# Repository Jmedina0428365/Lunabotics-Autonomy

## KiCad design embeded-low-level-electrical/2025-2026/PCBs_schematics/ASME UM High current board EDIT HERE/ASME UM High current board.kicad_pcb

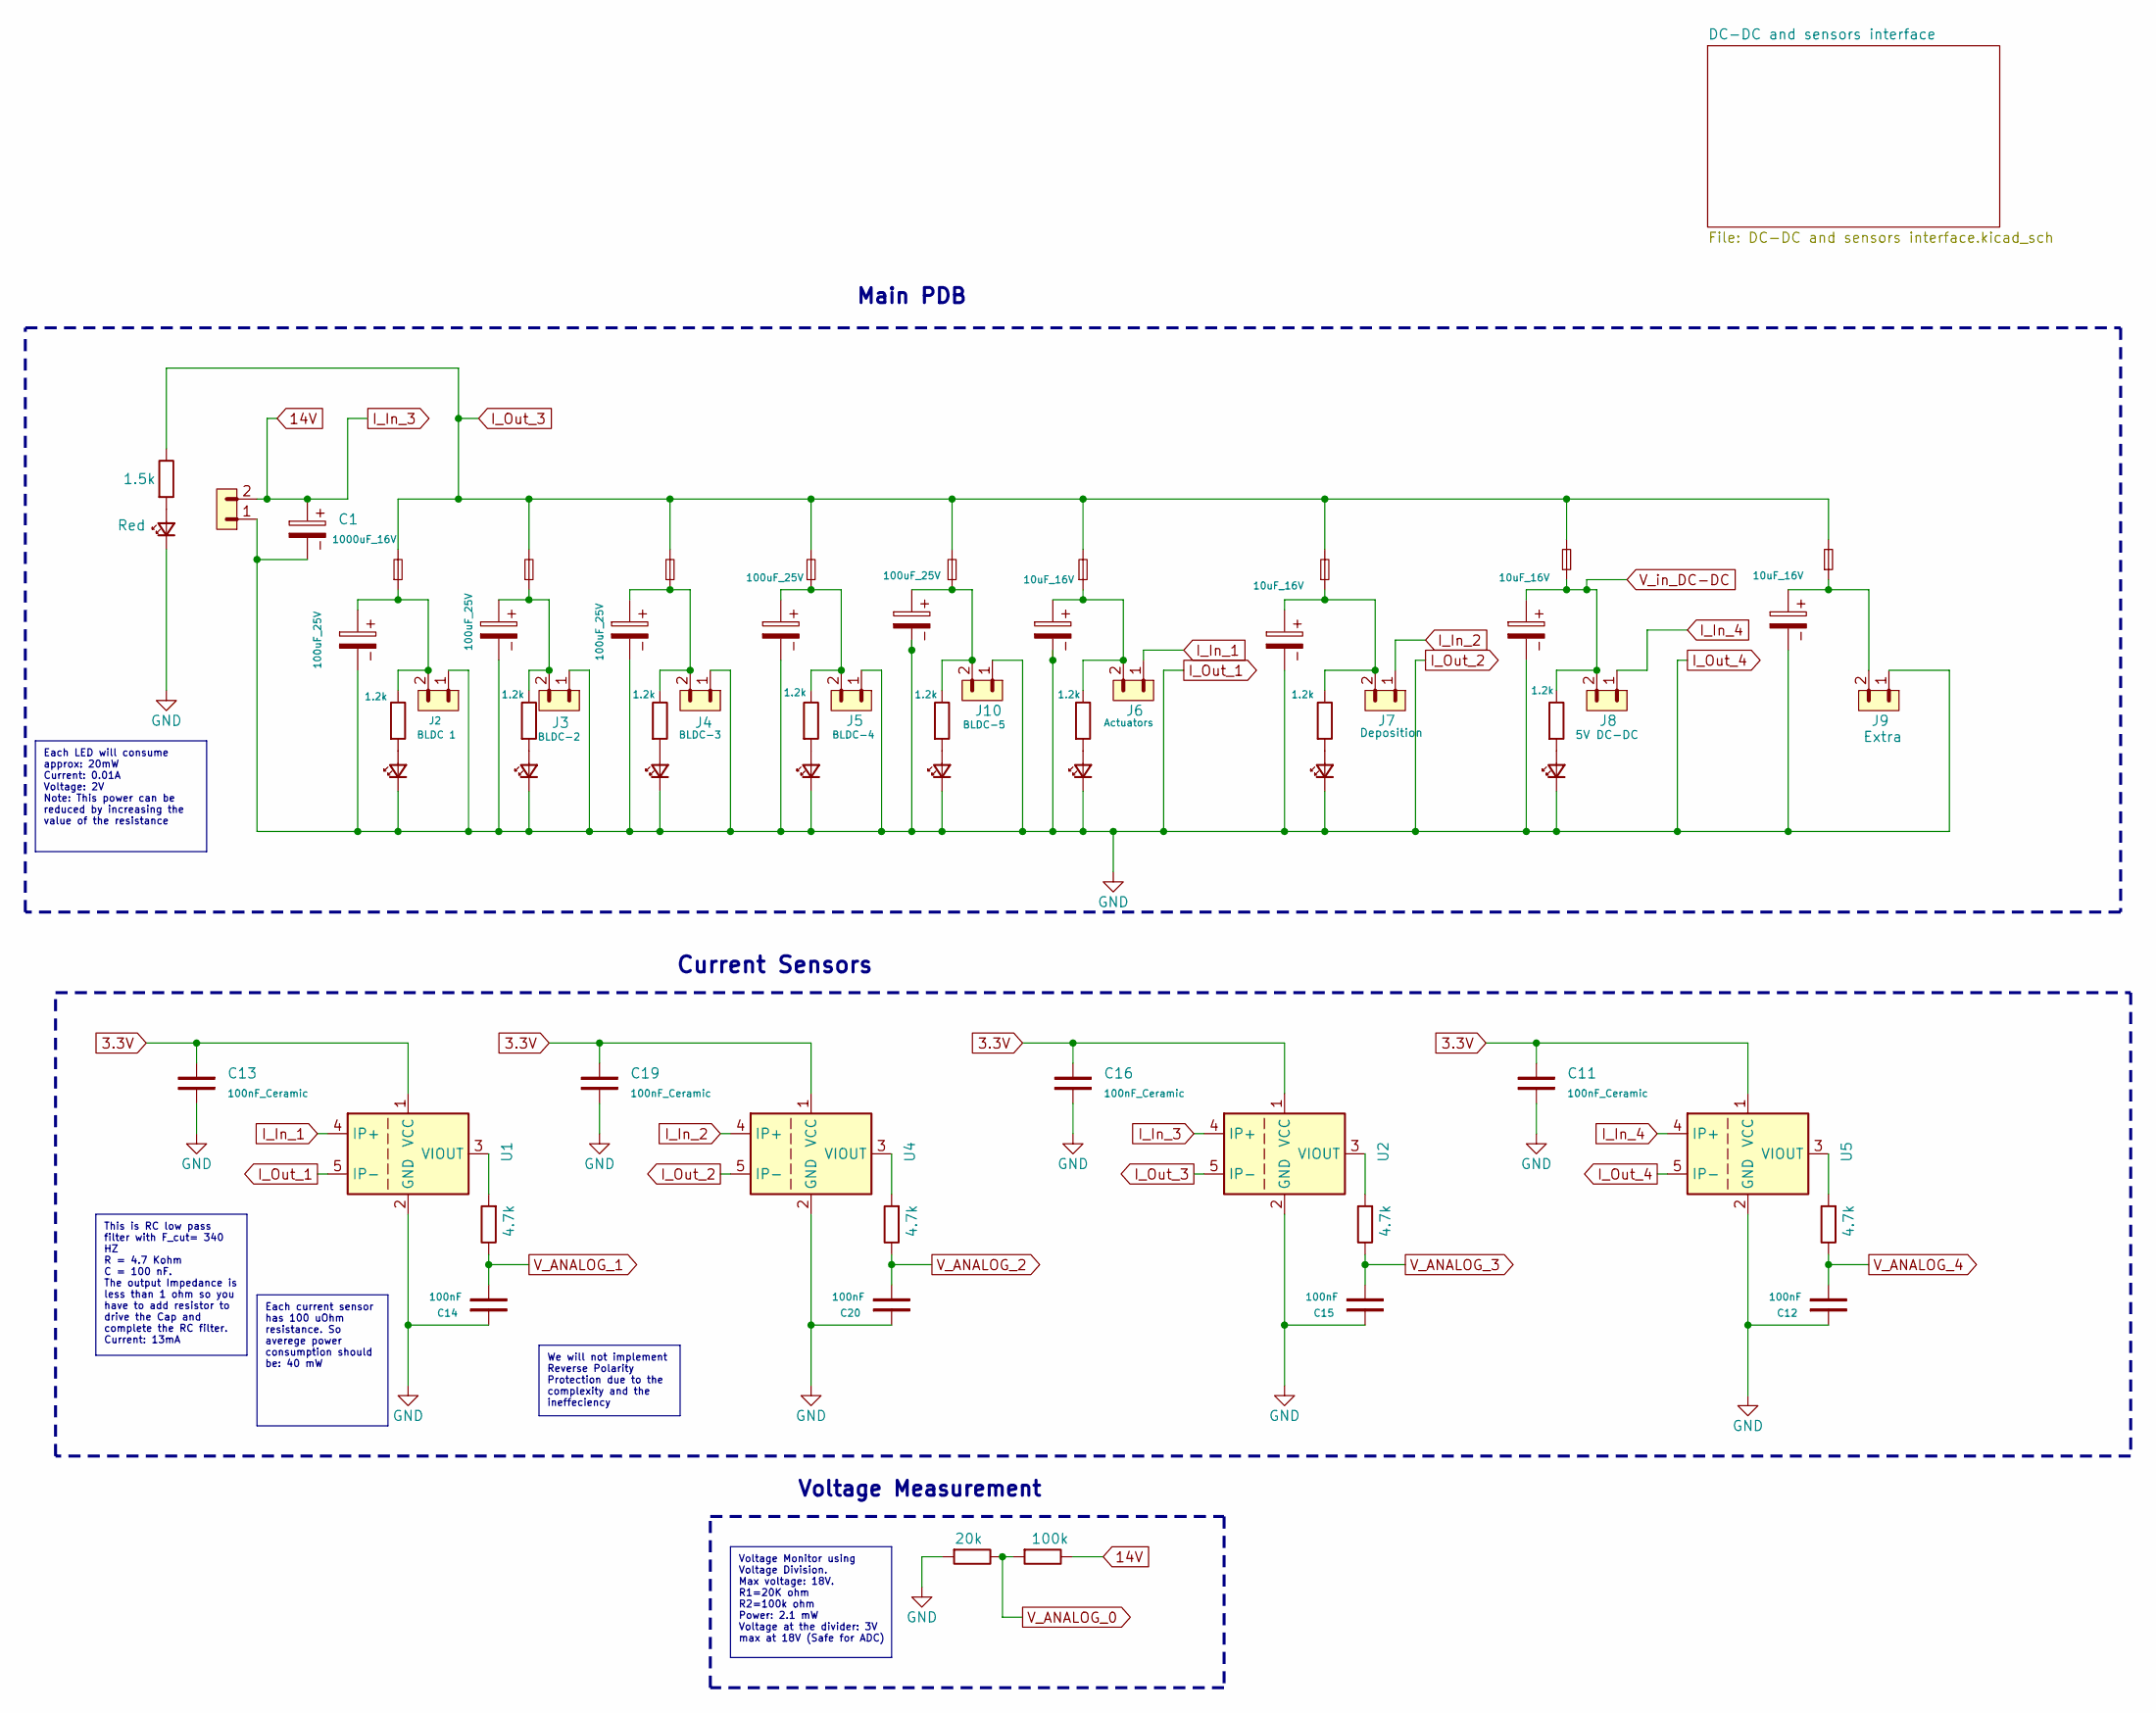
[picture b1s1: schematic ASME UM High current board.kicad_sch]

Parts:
C1: 1000uF_16V; CP_Radial_D10.0mm_P5.00mm
C2, C4, C5, C6: 10uF_16V; CP_Radial_D5.0mm_P2.00mm
C3, C7, C8, C9, C10: 100uF_25V; CP_Radial_D6.3mm_P2.50mm
C11, C13, C16, C19: 100nF_Ceramic; C_1206_3216Metric_Pad1.33x1.80mm_HandSolder
C12, C14, C15, C20: 100nF; C_1206_3216Metric_Pad1.33x1.80mm_HandSolder
D1: Red; LED_1206_3216Metric_Red
D2, D3, D4, D5, D6, D7, D8, D9: Green; LED_1206_3216Metric_Green
F1, F2, F3, F4, F5, F6, F7, F8, F9: Blade Fuse; Fuseholder_Automotive
J1: From main battery; AMASS_XT60-M_1x02_P7.20mm_Vertical
J2: BLDC 1; AMASS_XT60-M_1x02_P7.20mm_Vertical
J3: BLDC-2; AMASS_XT60-M_1x02_P7.20mm_Vertical
J4: BLDC-3; AMASS_XT60-M_1x02_P7.20mm_Vertical
J5: BLDC-4; AMASS_XT60-M_1x02_P7.20mm_Vertical
J6: Actuators; AMASS_XT60-M_1x02_P7.20mm_Vertical
J7: Deposition; AMASS_XT60-M_1x02_P7.20mm_Vertical
J8: 5V DC-DC; AMASS_XT60-M_1x02_P7.20mm_Vertical
J9: Extra; AMASS_XT60-M_1x02_P7.20mm_Vertical
J10: BLDC-5; AMASS_XT60-M_1x02_P7.20mm_Vertical
R1: 1.5k; R_1206_3216Metric_Pad1.30x1.75mm_HandSolder
R2, R3, R4, R5, R6, R7, R8, R9: 1.2k; R_1206_3216Metric_Pad1.30x1.75mm_HandSolder
R11, R12, R13, R16: 4.7k; R_1206_3216Metric_Pad1.30x1.75mm_HandSolder
R14: 20k; R_1206_3216Metric_Pad1.30x1.75mm_HandSolder
R15: 100k; R_1206_3216Metric_Pad1.30x1.75mm_HandSolder
U1, U4, U5: ACS758xCB-050B-PFF; Allegro_CB_PFF
U2: ACS772xCB-050B-PFF; Allegro_CB_PFF

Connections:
3.3V: C11.1, C13.1, C16.1, C19.1, U1.1 (VCC), U2.1 (VCC), U4.1 (VCC), U5.1 (VCC); also elsewhere on the board
14V: C1.1, J1.2, R15.2, U2.4 (IP+); also elsewhere on the board
I_In_1: J6.1, U1.4 (IP+)
I_In_2: J7.1, U4.4 (IP+)
I_In_4: J8.1, U5.4 (IP+); also elsewhere on the board
I_Out_1: C1.2, C2.2, C3.2, C4.2, C5.2, C6.2, C7.2, C8.2, C9.2, C10.2, C11.2, C12.1, C13.2, C14.1, C15.1, C16.2, C19.2, C20.1, D1.1 (K), D2.1 (K), D3.1 (K), D4.1 (K), D5.1 (K), D6.1 (K), D7.1 (K), D8.1 (K), D9.1 (K), J1.1, J2.1, J3.1, J4.1, J5.1, J9.1, J10.1, R14.1, U1.2 (GND), U1.5 (IP-), U2.2 (GND), U4.2 (GND), U4.5 (IP-), U5.2 (GND), U5.5 (IP-); also elsewhere on the board
I_Out_3: F1.2, F2.2, F3.2, F4.2, F5.2, F6.2, F7.2, F8.2, F9.2, R1.2, U2.5 (IP-)
unnamed: C2.1, F9.1, J9.2
unnamed: C3.1, F1.1, J2.2, R2.2
unnamed: C5.1, F7.1, J7.2, R7.2
unnamed: C6.1, F6.1, J6.2, R8.2
unnamed: C7.1, F4.1, J5.2, R5.2
unnamed: C8.1, F3.1, J4.2, R4.2
unnamed: C9.1, F2.1, J3.2, R3.2
unnamed: C10.1, F5.1, J10.2, R6.2
unnamed: D1.2 (A), R1.1
unnamed: D2.2 (A), R2.1
unnamed: D3.2 (A), R3.1
unnamed: D4.2 (A), R4.1
unnamed: D5.2 (A), R5.1
unnamed: D6.2 (A), R6.1
unnamed: D7.2 (A), R8.1
unnamed: D8.2 (A), R7.1
unnamed: D9.2 (A), R9.1
unnamed: R12.1, U1.3 (VIOUT)
unnamed: R13.1, U2.3 (VIOUT)
unnamed: R16.1, U4.3 (VIOUT)
unnamed: R11.1, U5.3 (VIOUT)
V_ANALOG_0: R14.2, R15.1; also elsewhere on the board
V_ANALOG_1: C14.2, R12.2; also elsewhere on the board
V_ANALOG_2: C20.2, R16.2; also elsewhere on the board
V_ANALOG_3: C15.2, R13.2; also elsewhere on the board
V_ANALOG_4: C12.2, R11.2; also elsewhere on the board
V_in_DC-DC: C4.1, F8.1, J8.2, R9.2; also elsewhere on the board

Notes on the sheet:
Current Sensors
Main PDB
Voltage Measurement
Voltage Monitor using Voltage Division. Max voltage: 18V. R1=20K ohm R2=100k ohm Power: 2.1 mW Voltage at the divider: 3V max at 18V (Safe for ADC)
Each LED will consume approx: 20mW Current: 0.01A Voltage: 2V Note: This power can be reduced by increasing the value of the resistance
We will not implement Reverse Polarity Protection due to the complexity and the ineffeciency
Each current sensor has 100 uOhm resistance. So averege power consumption should be: 40 mW
This is RC low pass filter with F_cut= 340 HZ R = 4.7 Kohm C = 100 nF. The output Impedance is less than 1 ohm so you have to add resistor to drive the Cap and complete the RC filter. Current: 13mA

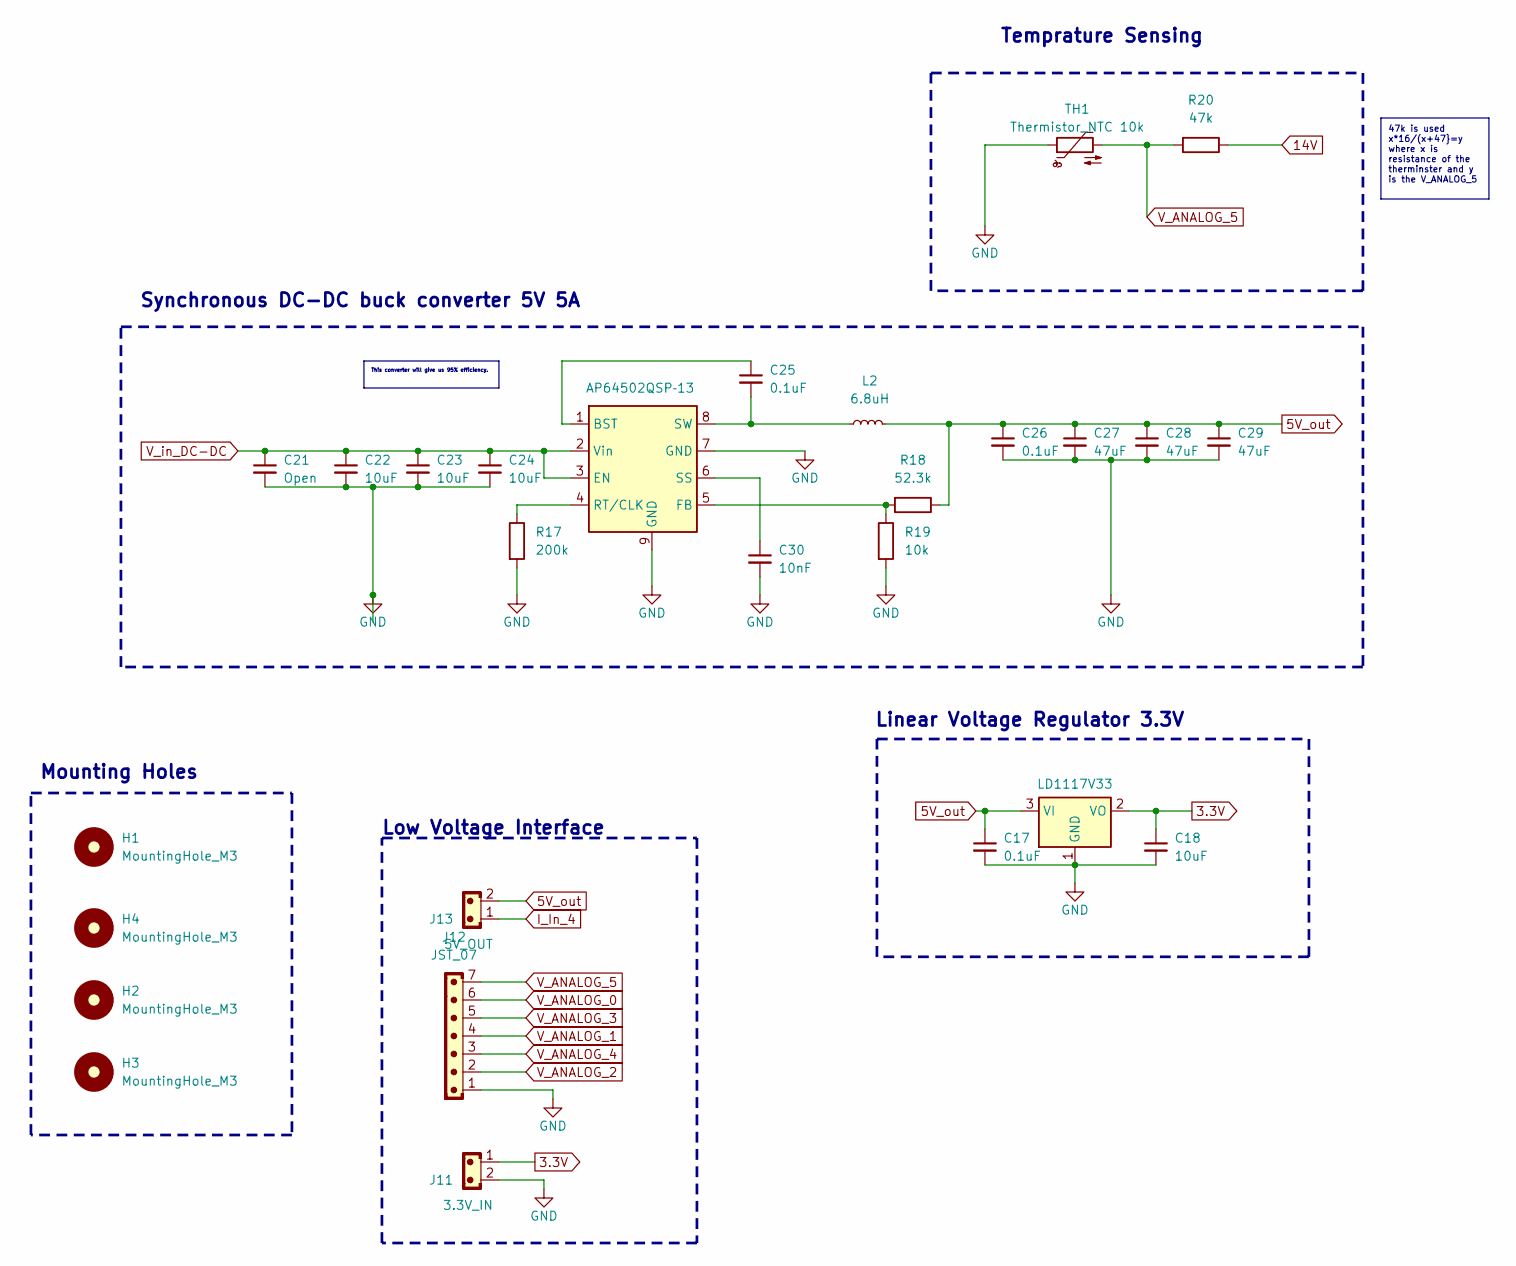
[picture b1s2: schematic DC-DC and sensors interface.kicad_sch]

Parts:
C17, C25, C26: 0.1uF; C_1206_3216Metric_Pad1.33x1.80mm_HandSolder; Voltage 25V; Tolerance 20%
C18: 10uF; CP_Radial_D5.0mm_P2.00mm; Voltage 25V; Tolerance 20%
C21: Open; C_1206_3216Metric_Pad1.33x1.80mm_HandSolder; Voltage 25V; Tolerance 20%
C22, C23, C24: 10uF; C_1206_3216Metric_Pad1.33x1.80mm_HandSolder; Voltage 25V; Tolerance 20%
C27, C28, C29: 47uF; C_1206_3216Metric_Pad1.33x1.80mm_HandSolder; Voltage 25V; Tolerance 20%
C30: 10nF; C_1206_3216Metric_Pad1.33x1.80mm_HandSolder; Voltage 25V; Tolerance 20%
H1, H2, H3, H4: MountingHole_M3; MountingHole_3.2mm_M3_DIN965_Pad_TopBottom
J11: 3.3V_IN; JST_EH_B2B-EH-A_1x02_P2.50mm_Vertical
J12: JST_07; JST_EH_B7B-EH-A_1x07_P2.50mm_Vertical
J13: 5V_OUT; AMASS_XT30U-M_1x02_P5.0mm_Vertical
L2: 6.8uH; IND_PCC-M1040LP_PAN-M
R17: 200k; R_1206_3216Metric_Pad1.30x1.75mm_HandSolder
R18: 52.3k; R_1206_3216Metric_Pad1.30x1.75mm_HandSolder
R19: 10k; R_1206_3216Metric_Pad1.30x1.75mm_HandSolder
R20: 47k; R_1206_3216Metric_Pad1.30x1.75mm_HandSolder
TH1: Thermistor_NTC 10k; 1210
U3: LD1117V33; TO-220-3_Vertical
U7: AP64502QSP‑13; Diodes_SO-8EP

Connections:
3.3V: C18.1, J11.1, U3.2 (VO); also elsewhere on the board
5V_out: C17.1, C26.1, C27.1, C28.1, C29.1, J13.2, L2.2, R18.1, U3.3 (VI)
14V: R20.1; also elsewhere on the board
I_In_4: J13.1; also elsewhere on the board
I_Out_1: C17.2, C18.2, C21.2, C22.2, C23.2, C24.2, C26.2, C27.2, C28.2, C29.2, C30.2, J11.2, J12.1, R17.2, R19.2, TH1.1, U3.1 (GND), U7.7 (GND), U7.9 (GND); also elsewhere on the board
unnamed: C25.1, U7.1 (BST)
unnamed: R18.2, R19.1, U7.5 (FB)
unnamed: R17.1, U7.4 (RT/CLK)
unnamed: C30.1, U7.6 (SS)
unnamed: C25.2, L2.1, U7.8 (SW)
V_ANALOG_0: J12.6; also elsewhere on the board
V_ANALOG_1: J12.4; also elsewhere on the board
V_ANALOG_2: J12.2; also elsewhere on the board
V_ANALOG_3: J12.5; also elsewhere on the board
V_ANALOG_4: J12.3; also elsewhere on the board
V_ANALOG_5: J12.7, R20.2, TH1.2
V_in_DC-DC: C21.1, C22.1, C23.1, C24.1, U7.2 (Vin), U7.3 (EN); also elsewhere on the board

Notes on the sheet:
Synchronous DC-DC buck converter 5V 5A
Mounting Holes
Temprature Sensing
Low Voltage Interface
Linear Voltage Regulator 3.3V
This converter will give us 95% efficiency.
47k is used x*16/(x+47}=y where x is resistance of the therminster and y is the V_ANALOG_5

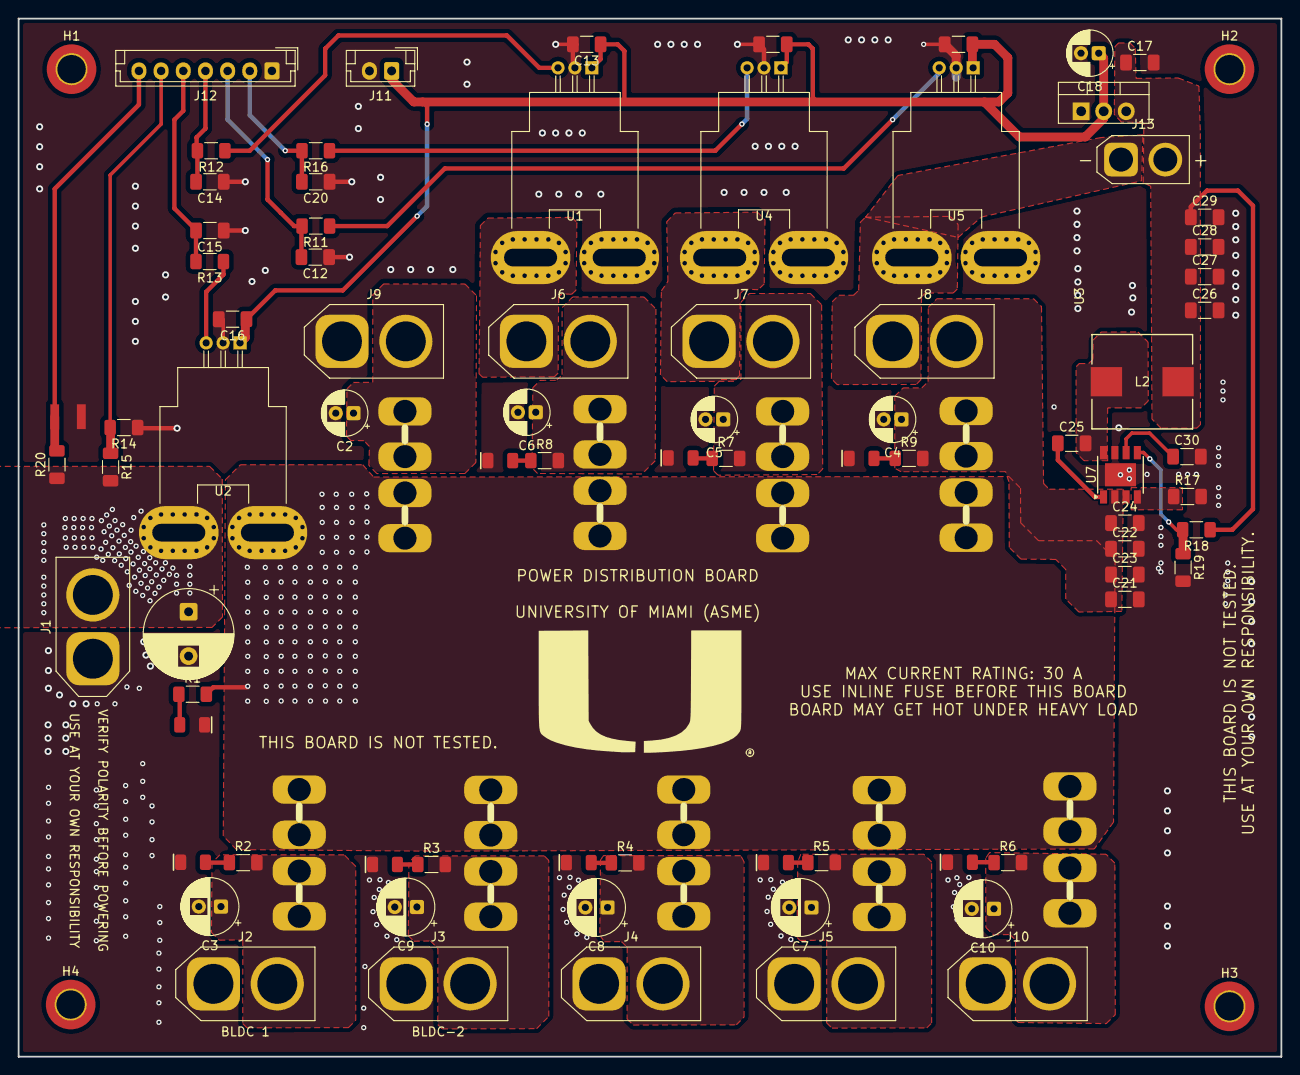
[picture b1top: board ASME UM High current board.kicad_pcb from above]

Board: 2 copper layers, 142.4 x 117.1 mm, 92 parts (0 on the bottom side), 41 nets.

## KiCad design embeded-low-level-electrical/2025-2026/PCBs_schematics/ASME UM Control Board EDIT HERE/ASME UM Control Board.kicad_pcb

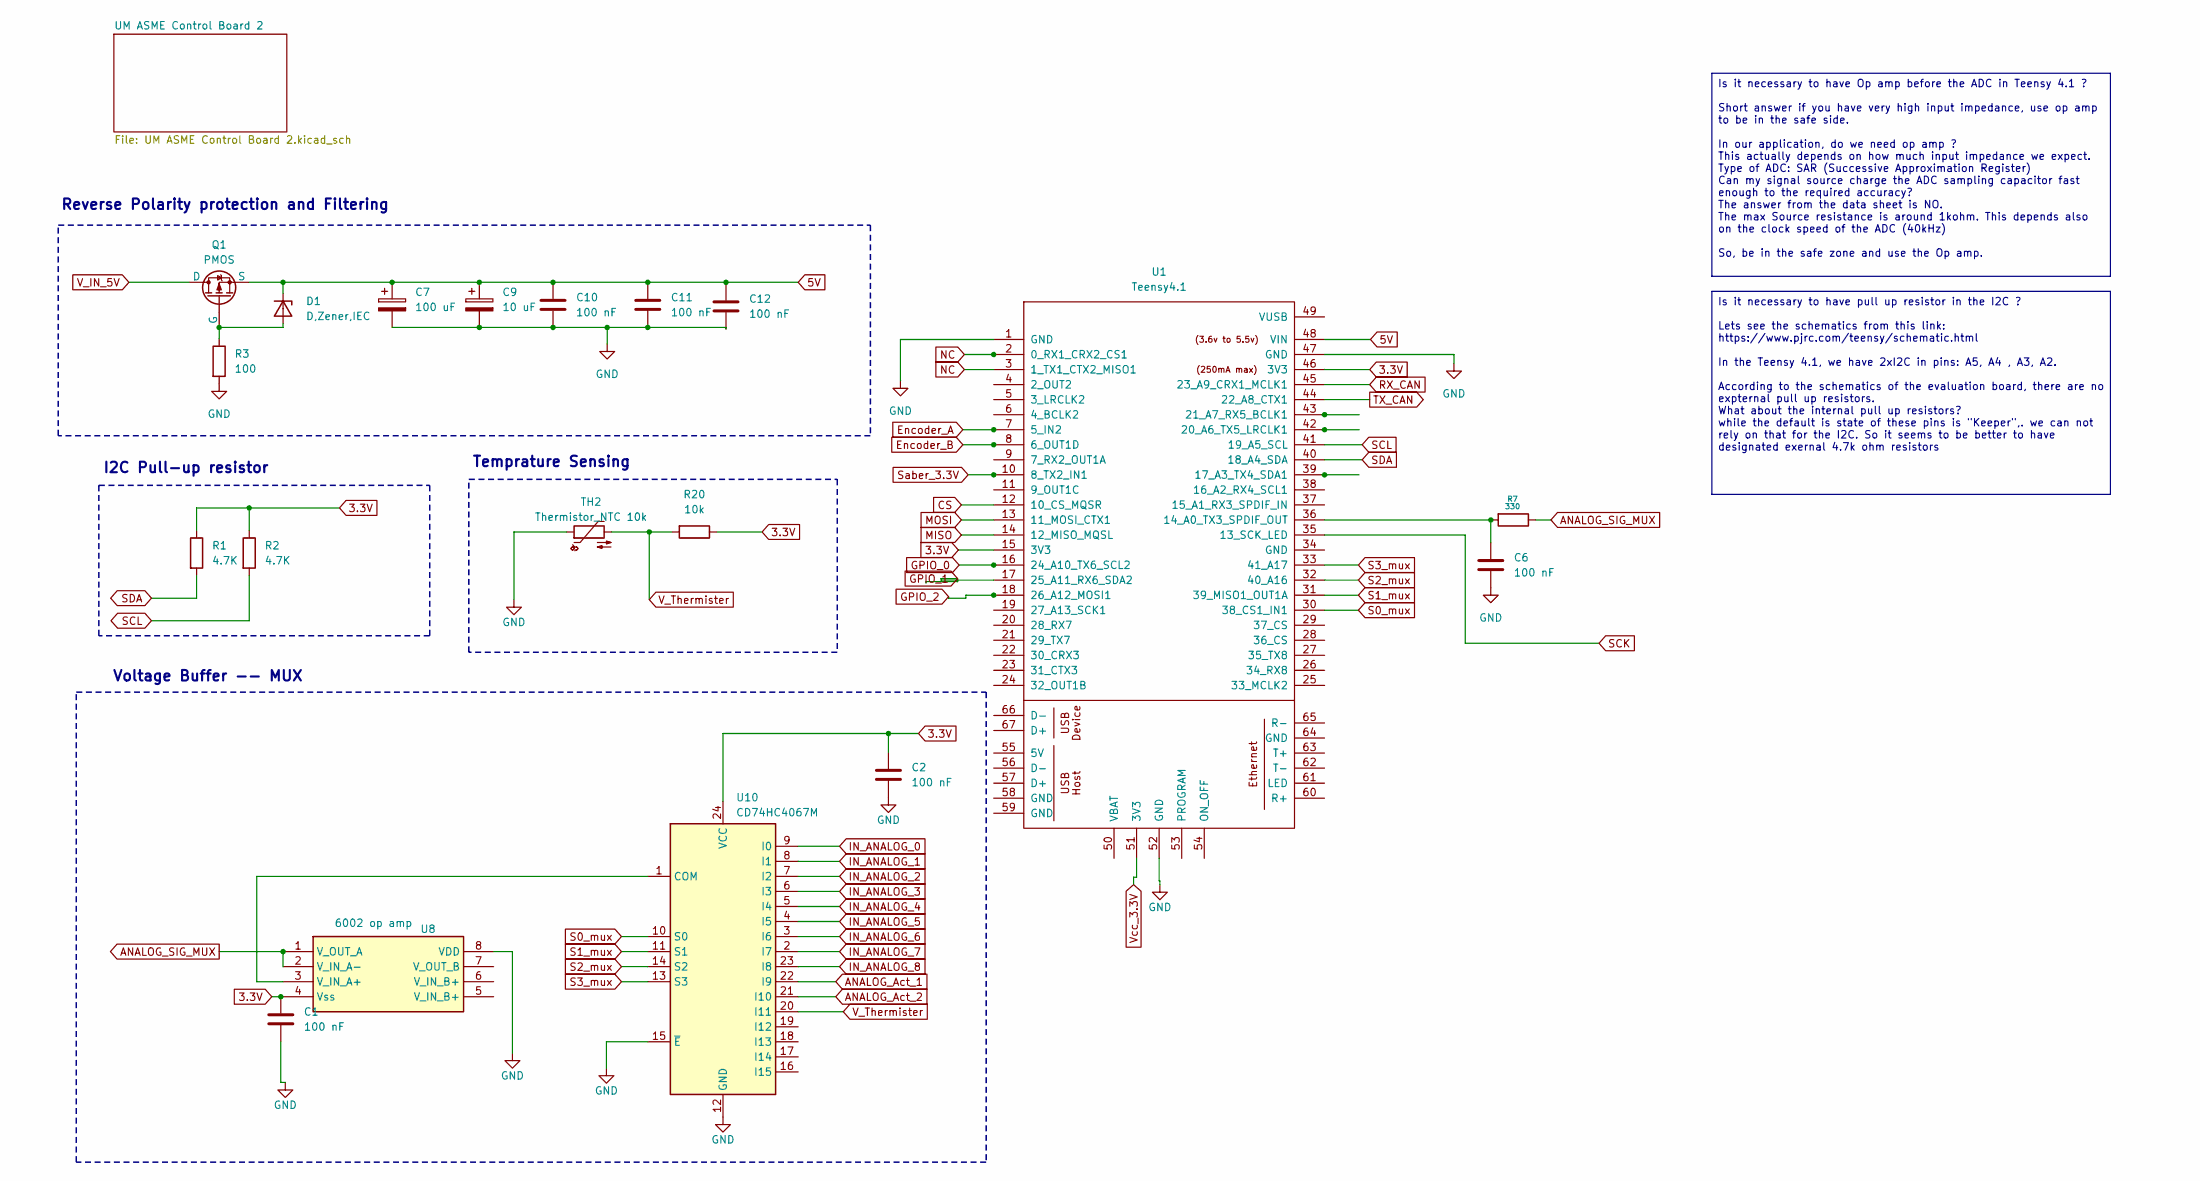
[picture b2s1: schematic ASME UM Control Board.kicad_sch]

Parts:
C1, C2, C6, C10, C11, C12: 100 nF; C_1206_3216Metric_Pad1.33x1.80mm_HandSolder
C7: 100 uF; CP_Radial_D8.0mm_P2.50mm
C9: 10 uF; C_1206_3216Metric_Pad1.33x1.80mm_HandSolder
D1: D,Zener,IEC; D_DO-35_SOD27_P7.62mm_Horizontal
Q1: PMOS; TO-220-3_Vertical
R1, R2: 4.7K; R_1206_3216Metric_Pad1.30x1.75mm_HandSolder
R3: 100; R_1206_3216Metric_Pad1.30x1.75mm_HandSolder
R7: 330; R_1206_3216Metric_Pad1.30x1.75mm_HandSolder
R20: 10k; R_1206_3216Metric_Pad1.30x1.75mm_HandSolder
TH2: Thermistor_NTC 10k; 1210
U1: Teensy4.1; Teensy41
U8: 6002 op amp; DIP-8_W7.62mm_LongPads
U10: CD74HC4067M; SOIC-24W_7.5x15.4mm_P1.27mm

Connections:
3.3V: C1.1, C2.1, R1.1, R2.1, R20.1, U1.15 (3V3), U1.46 (3V3), U8.4 (Vss), U10.24 (VCC); also elsewhere on the board
5V: C7.1, C9.1, C10.1, C11.1, C12.1, D1.1 (K-), Q1.3 (S), U1.48 (VIN); also elsewhere on the board
ANALOG_Act_1: U10.22 (I9); also elsewhere on the board
ANALOG_Act_2: U10.21 (I10); also elsewhere on the board
ANALOG_SIG_MUX: R7.1, U8.1 (V_OUT_A), U8.2 (V_IN_A-)
CS: U1.12 (10_CS_MQSR)
Encoder_A: U1.7 (5_IN2); also elsewhere on the board
Encoder_B: U1.8 (6_OUT1D); also elsewhere on the board
GND: C1.2, C2.2, C6.2, C7.2, C9.2, C10.2, C11.2, C12.2, R3.2, TH2.1, U1.1 (GND), U1.47 (GND), U1.52 (GND), U8.8 (VDD), U10.12 (GND), U10.15 (~E); also elsewhere on the board
GPIO_0: U1.16 (24_A10_TX6_SCL2); also elsewhere on the board
GPIO_1: U1.17 (25_A11_RX6_SDA2); also elsewhere on the board
GPIO_2: U1.18 (26_A12_MOSI1); also elsewhere on the board
IN_ANALOG_0: U10.9 (I0); also elsewhere on the board
IN_ANALOG_1: U10.8 (I1); also elsewhere on the board
IN_ANALOG_2: U10.7 (I2); also elsewhere on the board
IN_ANALOG_3: U10.6 (I3); also elsewhere on the board
IN_ANALOG_4: U10.5 (I4); also elsewhere on the board
IN_ANALOG_5: U10.4 (I5); also elsewhere on the board
IN_ANALOG_6: U10.3 (I6); also elsewhere on the board
IN_ANALOG_7: U10.2 (I7); also elsewhere on the board
IN_ANALOG_8: U10.23 (I8); also elsewhere on the board
MISO: U1.14 (12_MISO_MQSL)
MOSI: U1.13 (11_MOSI_CTX1)
NC: U1.2 (0_RX1_CRX2_CS1), U1.3 (1_TX1_CTX2_MISO1)
unnamed: D1.2 (A+), Q1.2 (G), R3.1
unnamed: C6.1, R7.2, U1.36 (14_A0_TX3_SPDIF_OUT)
unnamed: U8.3 (V_IN_A+), U10.1 (COM)
RX_CAN: U1.45 (23_A9_CRX1_MCLK1); also elsewhere on the board
S0_mux: U1.30 (38_CS1_IN1), U10.10 (S0)
S1_mux: U1.31 (39_MISO1_OUT1A), U10.11 (S1)
S2_mux: U1.32 (40_A16), U10.14 (S2)
S3_mux: U1.33 (41_A17), U10.13 (S3)
SCK: U1.35 (13_SCK_LED)
SCL: R2.2, U1.41 (19_A5_SCL); also elsewhere on the board
SDA: R1.2, U1.40 (18_A4_SDA); also elsewhere on the board
Saber_3.3V: U1.10 (8_TX2_IN1); also elsewhere on the board
TX_CAN: U1.44 (22_A8_CTX1); also elsewhere on the board
V_IN_5V: Q1.1 (D); also elsewhere on the board
V_Thermister: R20.2, TH2.2, U10.20 (I11)

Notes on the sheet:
Voltage Buffer -- MUX
Temprature Sensing
Reverse Polarity protection and Filtering
I2C Pull-up resistor
Is it necessary to have Op amp before the ADC in Teensy 4.1 ? Short answer if you have very high input impedance, use op amp to be in the safe side. In our application, do we need op amp ? This actually depends on how much input impedance we expect. Type of ADC: SAR (Successive Approximation Regist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
Is it necessary to have pull up resistor in the I2C ? Lets see the schematics from this link: https://www.pjrc.com/teensy/schematic.html In the Teensy 4.1, we have 2xI2C in pins: A5, A4 , A3, A2. According to the schematics of the evaluation board, there are no expternal pull up resistors. What abo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

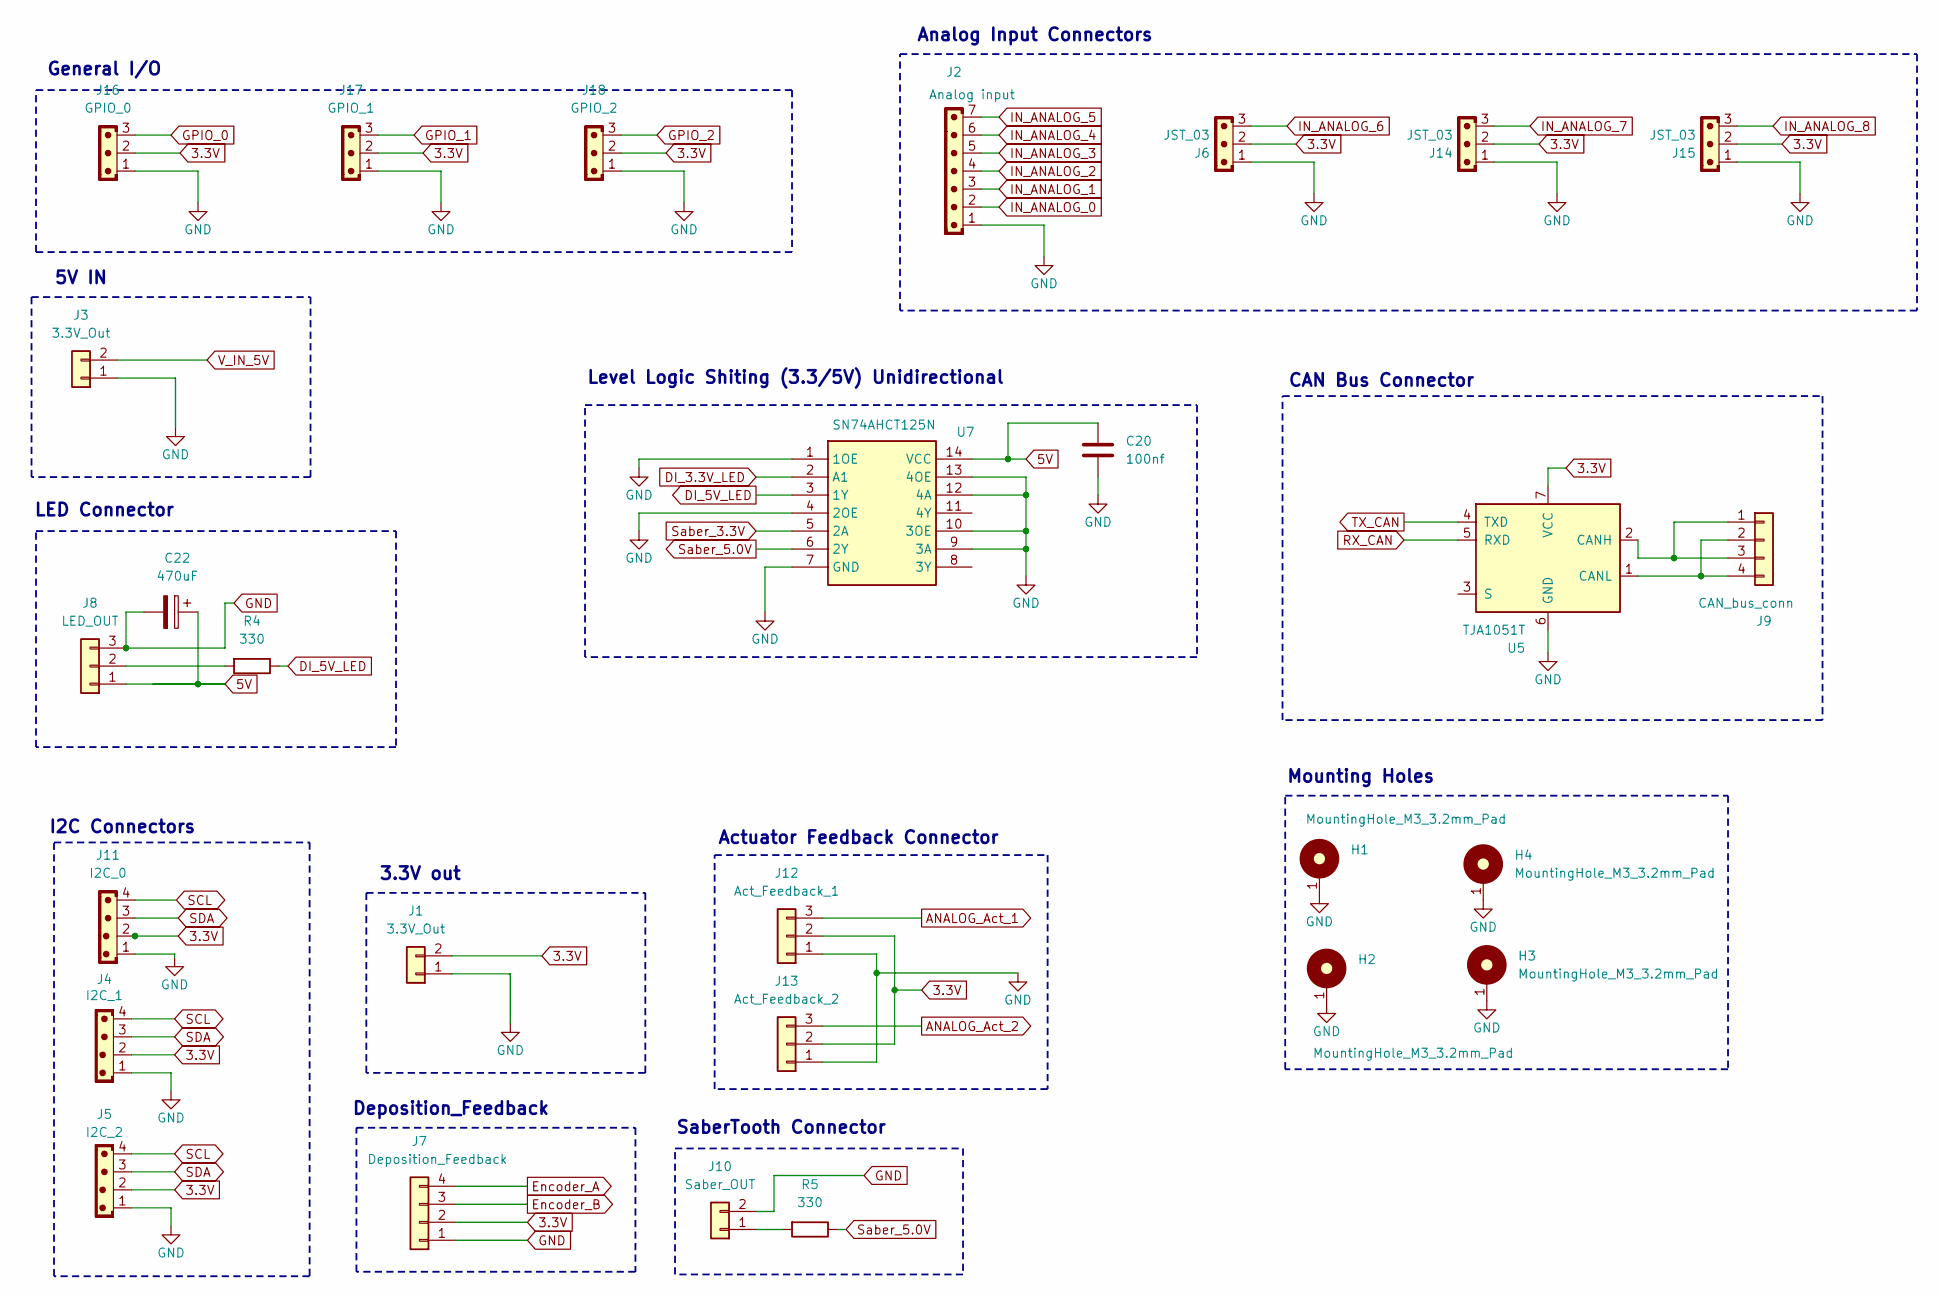
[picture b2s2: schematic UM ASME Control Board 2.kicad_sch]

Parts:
C20: 100nf; C_1206_3216Metric_Pad1.33x1.80mm_HandSolder
C22: 470uF; CP_Radial_D10.0mm_P3.80mm
H1, H2, H3, H4: MountingHole_M3_3.2mm_Pad; MountingHole_3.2mm_Pad
J1: 3.3V_Out; JST_PH_B2B-PH-K_1x02_P2.00mm_Vertical
J2: Analog input; JST_PH_B7B-PH-K_1x07_P2.00mm_Vertical
J3: 3.3V_Out; AMASS_XT30UPB-M_1x02_P5.0mm_Vertical
J4: I2C_1; JST_PH_B4B-PH-K_1x04_P2.00mm_Vertical
J5: I2C_2; JST_PH_B4B-PH-K_1x04_P2.00mm_Vertical
J6, J14, J15: JST_03; JST_PH_B3B-PH-K_1x03_P2.00mm_Vertical
J7: Deposition_Feedback; JST_PH_B4B-PH-K_1x04_P2.00mm_Vertical
J8: LED_OUT; JST_EH_B3B-EH-A_1x03_P2.50mm_Vertical
J9: CAN_bus_conn; JST_PH_B4B-PH-K_1x04_P2.00mm_Vertical
J10: Saber_OUT; JST_PH_B2B-PH-K_1x02_P2.00mm_Vertical
J11: I2C_0; JST_PH_B4B-PH-K_1x04_P2.00mm_Vertical
J12: Act_Feedback_1; JST_PH_B3B-PH-K_1x03_P2.00mm_Vertical
J13: Act_Feedback_2; JST_PH_B3B-PH-K_1x03_P2.00mm_Vertical
J16: GPIO_0; JST_PH_B3B-PH-K_1x03_P2.00mm_Vertical
J17: GPIO_1; JST_PH_B3B-PH-K_1x03_P2.00mm_Vertical
J18: GPIO_2; JST_PH_B3B-PH-K_1x03_P2.00mm_Vertical
R4, R5: 330; R_1206_3216Metric_Pad1.30x1.75mm_HandSolder
U5: TJA1051T; PinHeader_1x07_P2.54mm_Vertical
U7: SN74AHCT125N; DIP-14_W7.62mm_LongPads

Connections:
3.3V: J1.2, J4.2, J5.2, J6.2, J7.2, J11.2, J12.2, J13.2, J14.2, J15.2, J16.2, J17.2, J18.2, U5.7 (VCC); also elsewhere on the board
5V: C20.2, C22.1, J8.1, U7.14 (VCC); also elsewhere on the board
ANALOG_Act_1: J12.3; also elsewhere on the board
ANALOG_Act_2: J13.3; also elsewhere on the board
DI_3.3V_LED: U7.2 (A1)
DI_5V_LED: R4.1, U7.3 (1Y)
Encoder_A: J7.4; also elsewhere on the board
Encoder_B: J7.3; also elsewhere on the board
GND: C20.1, C22.2, H1.1, H2.1, H3.1, H4.1, J1.1, J2.1, J3.1, J4.1, J5.1, J6.1, J7.1, J8.3, J10.2, J11.1, J12.1, J13.1, J14.1, J15.1, J16.1, J17.1, J18.1, U5.6 (GND), U7.1 (1OE), U7.4 (2OE), U7.7 (GND), U7.9 (3A), U7.10 (3OE), U7.12 (4A), U7.13 (4OE); also elsewhere on the board
GPIO_0: J16.3; also elsewhere on the board
GPIO_1: J17.3; also elsewhere on the board
GPIO_2: J18.3; also elsewhere on the board
IN_ANALOG_0: J2.2; also elsewhere on the board
IN_ANALOG_1: J2.3; also elsewhere on the board
IN_ANALOG_2: J2.4; also elsewhere on the board
IN_ANALOG_3: J2.5; also elsewhere on the board
IN_ANALOG_4: J2.6; also elsewhere on the board
IN_ANALOG_5: J2.7; also elsewhere on the board
IN_ANALOG_6: J6.3; also elsewhere on the board
IN_ANALOG_7: J14.3; also elsewhere on the board
IN_ANALOG_8: J15.3; also elsewhere on the board
unnamed: J8.2, R4.2
unnamed: J9.1, J9.3, U5.2 (CANH)
unnamed: J9.2, J9.4, U5.1 (CANL)
unnamed: J10.1, R5.2
RX_CAN: U5.5 (RXD); also elsewhere on the board
SCL: J4.4, J5.4, J11.4; also elsewhere on the board
SDA: J4.3, J5.3, J11.3; also elsewhere on the board
Saber_3.3V: U7.5 (2A); also elsewhere on the board
Saber_5.0V: R5.1, U7.6 (2Y)
TX_CAN: U5.4 (TXD); also elsewhere on the board
V_IN_5V: J3.2; also elsewhere on the board

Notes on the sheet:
3.3V out
I2C Connectors
Deposition_Feedback
Level Logic Shiting (3.3/5V) Unidirectional
Mounting Holes
LED Connector
General I/O
5V IN
Actuator Feedback Connector
CAN Bus Connector
Analog Input Connectors
SaberTooth Connector

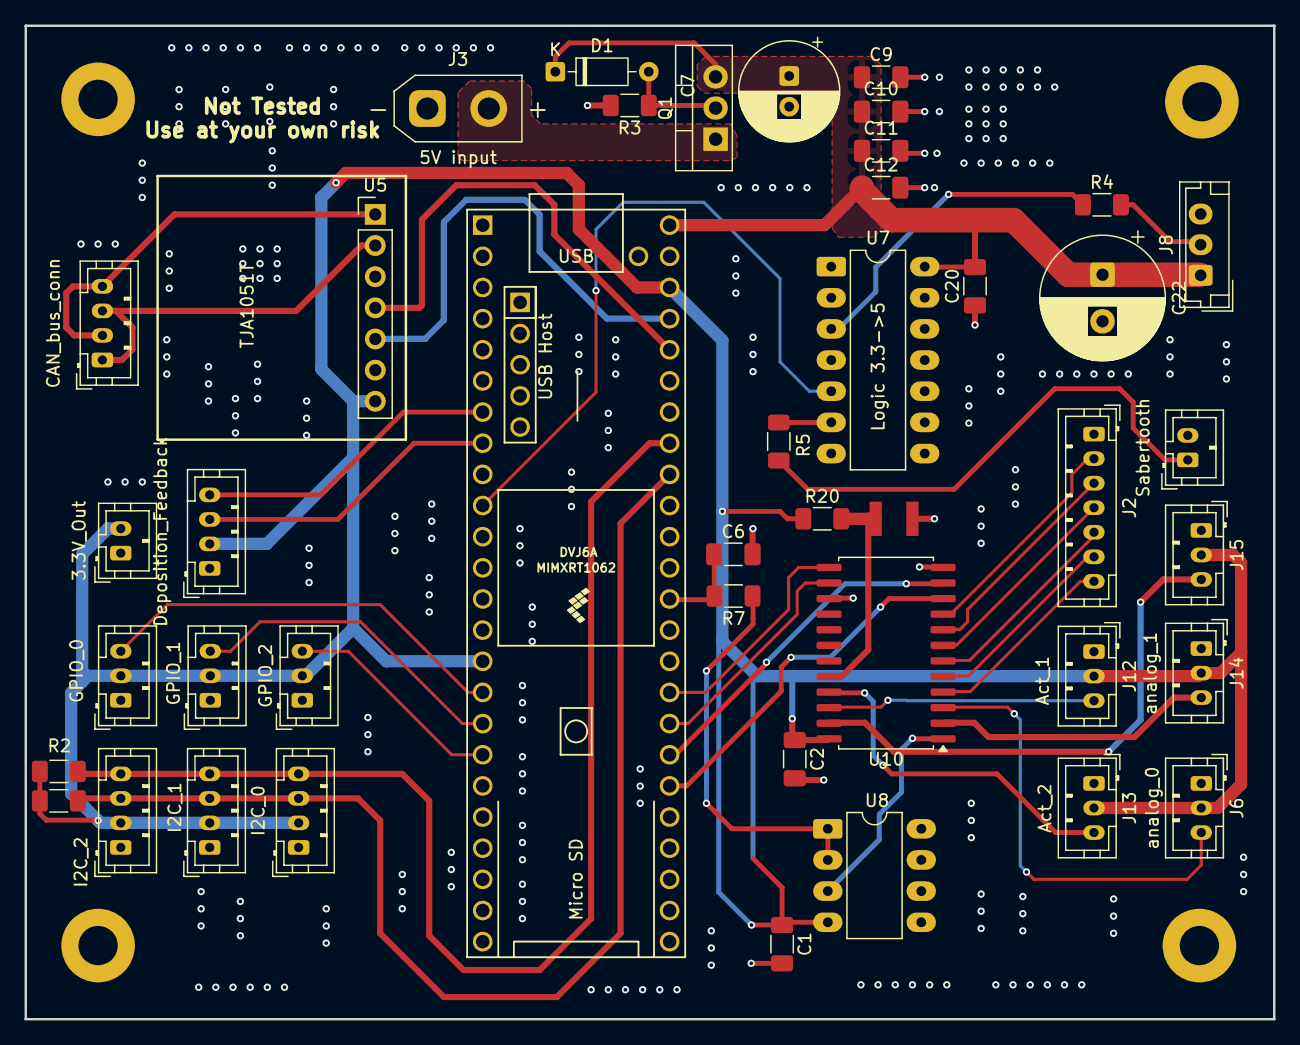
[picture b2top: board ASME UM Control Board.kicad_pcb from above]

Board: 4 copper layers, 101.8 x 81.0 mm, 47 parts (0 on the bottom side), 41 nets.
